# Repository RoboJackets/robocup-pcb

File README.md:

RoboCup PCB Repository
===========
Welcome to the Georgia Tech RoboJackets repository for management and storage of RoboCup's hardware files! Additional information about the team and current projects can be found on the [RoboJackets Website](http://www.robojackets.org/teams/robocup/) and the [RoboJacket Wiki](http://wiki.robojackets.org/w/RoboCup).

If you are a new member to the RoboCup electrical team and have never used *[git version control](http://git-scm.com/)* before, we highly recommend that you familiarize yourself with it by reading [this guide](https://git-scm.com/book/en/v2).

## Prerequisites
- A computer configured with git [[Linux (Preferred)](https://git-scm.com/install/linux)] [[Windows](https://windows.github.com)] [[Mac](https://mac.github.com/)]
- An installation of [KiCAD v10.0](http://kicad-pcb.org/download/)
- An installation of [Obsidian](https://obsidian.md/download)

## Setup

### Cloning the Repository
To clone the repository, run the following command in your terminal:
```
git clone git@github.com:RoboJackets/robocup-pcb.git
```

## Board Archives
All currently deployed boards as of 2026 were designed using KiCAD.

However, older boards in the archives were designed using [EAGLE](http://www.cadsoftusa.com/) or [PCB](http://pcb.geda-project.org) (a program that is part of the [gEDA project](http://www.geda-project.org))

Unfortunately, EAGLE and PCB are no longer supported by their respective companies, and are not available for download. If you need access to these files, you are on your own.

## License

This project is licensed under the Apache License v2.0.  See the [LICENSE](LICENSE) file for more information.

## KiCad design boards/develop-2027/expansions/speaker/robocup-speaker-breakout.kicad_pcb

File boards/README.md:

# Style Guide

## Schematic Style
* Always snap to 0.1 inch grid
* Insert appropriate size frame for each sheet
    * Set Global Attributes for `REVISION` and `TEAM`
    * Set Attribute of frame for `SCH_DESC`

## Board Style
* Attempt to keep snapped to 0.5 mm (with 0.25 alt) with 90º or 45º angles

## Library Style
#### Symbol
* Always keep pins aligned to 0.1 inch grid
* Add Name and Value on correct layers

#### Package
* Add Name and Value on correct layers
* Silkscreen on `TPLACE` should not go over pad
* Use `TDOCU` to show accurate package outline

#### Device
* Final Device ideally be actual part number unless generic part where many possibles could be used
* Use wildcard when using multiple packages with one symbol
* Add correct prefix for component type ([reference](https://en.wikipedia.org/wiki/Reference_designator)), common components:
    * C : Capacitor
    * L : Inductor
    * R : Resistor
    * D : Diodes (including LEDs)
    * J : Jack (least movable part of connector)
    * Q : Transistor
    * F : Fuse
* Add manufacturer part number and (when possible) Digikey part number as attributes `MPN` and `DIGIKEY` respectivly
    * Do this for each technology and variant combination

# Finalize Board

When board completely done and ready to order ensure the following are completed:
* Board folder named "board-name"-v"version"
* Export board to PNG and place in folder
* Create README.md with description of the board and PNG of the board
* Create gerber.zip file of all Gerber files to be sent to board fab
* After all items added for board, make final commit for board version and tag commit as "board-name"-v"version"
* Once pushed to Github create release of board from tag consisting of list of changes from past version, link to gerber.zip (Github raw link for that tag), and PNG of board
    * For prototypes mark release as pre-release

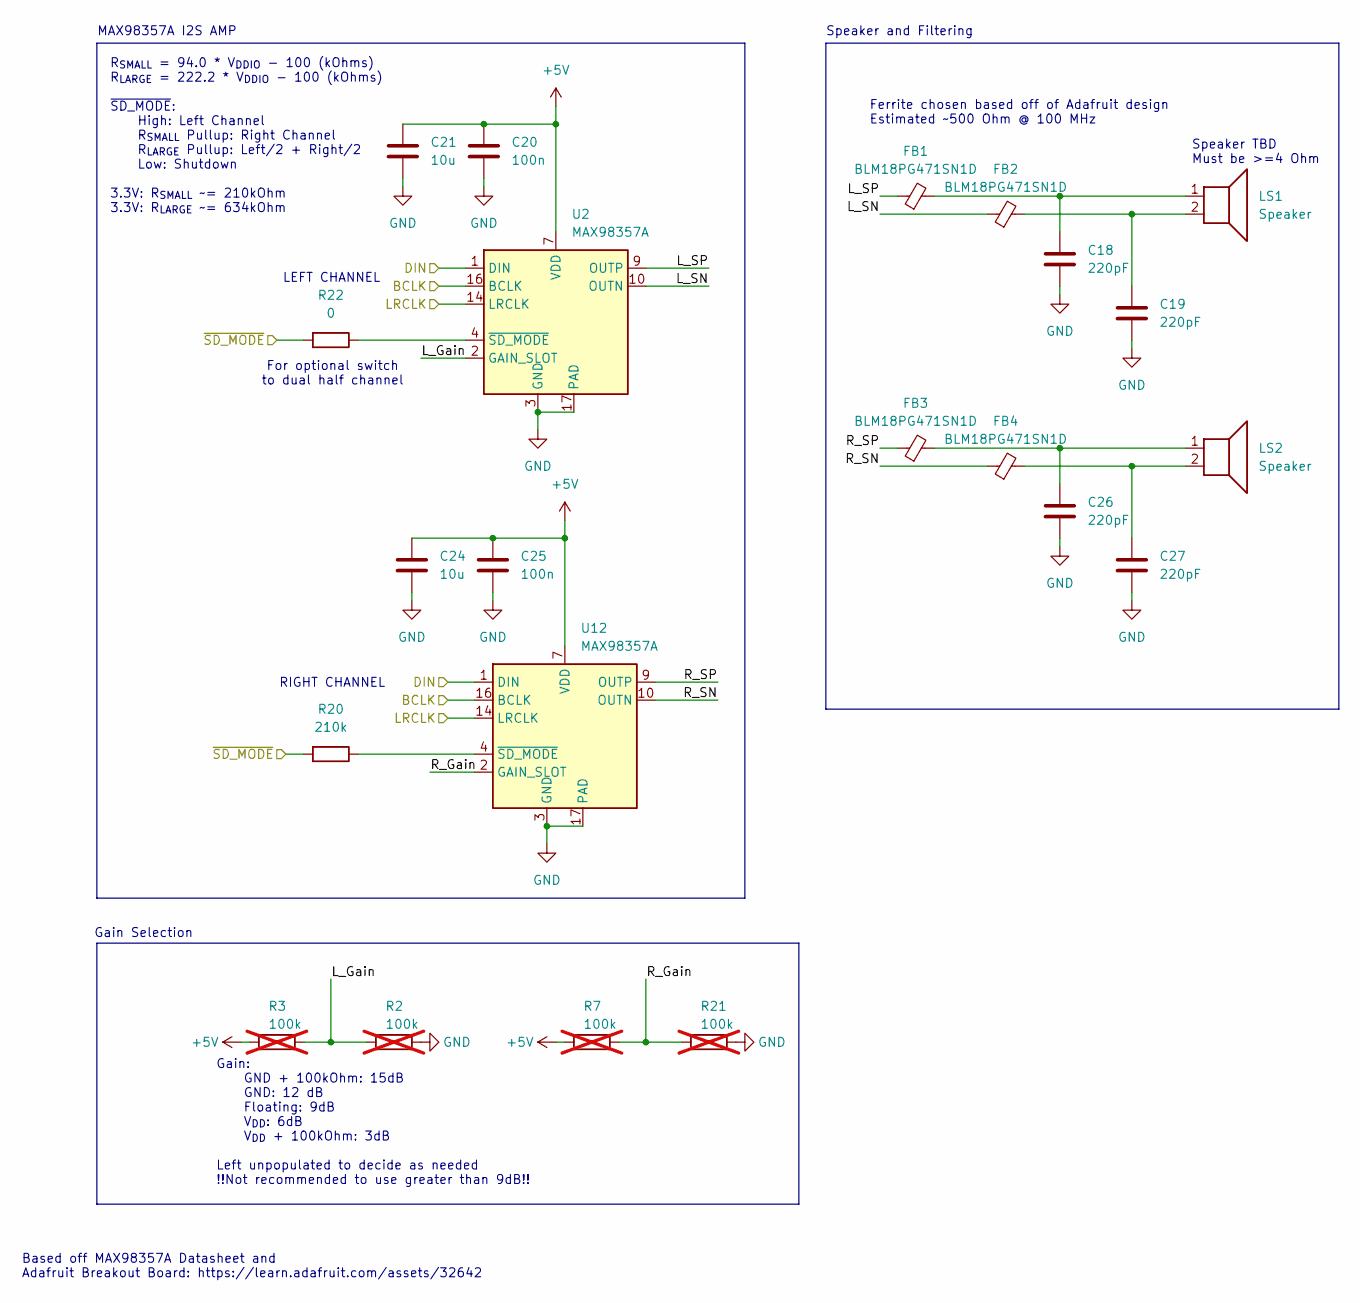
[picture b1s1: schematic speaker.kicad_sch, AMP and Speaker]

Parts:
C18, C19, C26, C27: 220pF; C_0402_1005Metric; Manufacturer P/N GCM1555C1H221FA16D
C20, C25: 100n; C_0402_1005Metric; Manufacturer P/N CC0402JRX7R7BB104
C21, C24: 10u; C_0603_1608Metric; Manufacturer P/N GRM188R61A106ME69J
FB1, FB2, FB3, FB4: BLM18PG471SN1D; L_0603_1608Metric; Manufacturer P/N BLM18PG471SN1D
LS1, LS2: Speaker; JST_GH_SM02B-GHS-TB_1x02-1MP_P1.25mm_Horizontal; Manufacturer P/N SM02B-GHS-TB
R2, R3, R7, R21: 100k; R_0402_1005Metric; Manufacturer P/N ERJ-2GEJ104X; not fitted
R20: 210k; R_0402_1005Metric; Manufacturer P/N RK73H1ETTP2103F
R22: 0; R_0402_1005Metric; Manufacturer P/N ERJ-2GE0R00X
U2, U12: MAX98357A; TQFN-16-1EP_3x3mm_P0.5mm_EP1.23x1.23mm; Manufacturer P/N MAX98357AETE+T

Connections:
+5V: C20.1, C21.1, C24.1, C25.1, R3.1, R7.1, U2.7 (VDD), U2.8 (VDD), U12.7 (VDD), U12.8 (VDD); also elsewhere on the board
/MCU/BCLK: U2.16 (BCLK), U12.16 (BCLK); also elsewhere on the board
/MCU/DIN: U2.1 (DIN), U12.1 (DIN); also elsewhere on the board
/MCU/LRCLK: U2.14 (LRCLK), U12.14 (LRCLK); also elsewhere on the board
/MCU/~SD_MODE: R20.2, R22.2; also elsewhere on the board
/Speaker/L_Gain: R2.1, R3.2, U2.2 (GAIN_SLOT)
/Speaker/L_SN: FB2.1, U2.10 (OUTN)
/Speaker/L_SP: FB1.1, U2.9 (OUTP)
/Speaker/R_Gain: R7.2, R21.1, U12.2 (GAIN_SLOT)
/Speaker/R_SN: FB4.1, U12.10 (OUTN)
/Speaker/R_SP: FB3.1, U12.9 (OUTP)
GND: C18.2, C19.2, C20.2, C21.2, C24.2, C25.2, C26.2, C27.2, R2.2, R21.2, U2.3 (GND), U2.11 (GND), U2.15 (GND), U2.17 (PAD), U12.3 (GND), U12.11 (GND), U12.15 (GND), U12.17 (PAD); also elsewhere on the board
unnamed: C18.1, FB1.2, LS1.1
unnamed: C19.1, FB2.2, LS1.2
unnamed: C26.1, FB3.2, LS2.1
unnamed: C27.1, FB4.2, LS2.2
unnamed: R22.1, U2.4 (~SD_MODE)
unnamed: R20.1, U12.4 (~SD_MODE)

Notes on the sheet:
Based off MAX98357A Datasheet and Adafruit Breakout Board: https://learn.adafruit.com/assets/32642
LEFT CHANNEL
Gain Selection
RIGHT CHANNEL
Ferrite chosen based off of Adafruit design Estimated ~500 Ohm @ 100 MHz
MAX98357A I2S AMP
Speaker TBD Must be >=4 Ohm
R_{SMALL} = 94.0 * V_{DDIO} - 100 (kOhms) R_{LARGE} = 222.2 * V_{DDIO} - 100 (kOhms) ~{SD_MODE}: High: Left Channel R_{SMALL} Pullup: Right Channel R_{LARGE} Pullup: Left/2 + Right/2 Low: Shutdown 3.3V: R_{SMALL} ~= 210kOhm 3.3V: R_{LARGE} ~= 634kOhm
Speaker and Filtering
Gain: GND + 100kOhm: 15dB GND: 12 dB Floating: 9dB V_{DD}: 6dB V_{DD} + 100kOhm: 3dB Left unpopulated to decide as needed !!Not recommended to use greater than 9dB!!
For optional switch to dual half channel

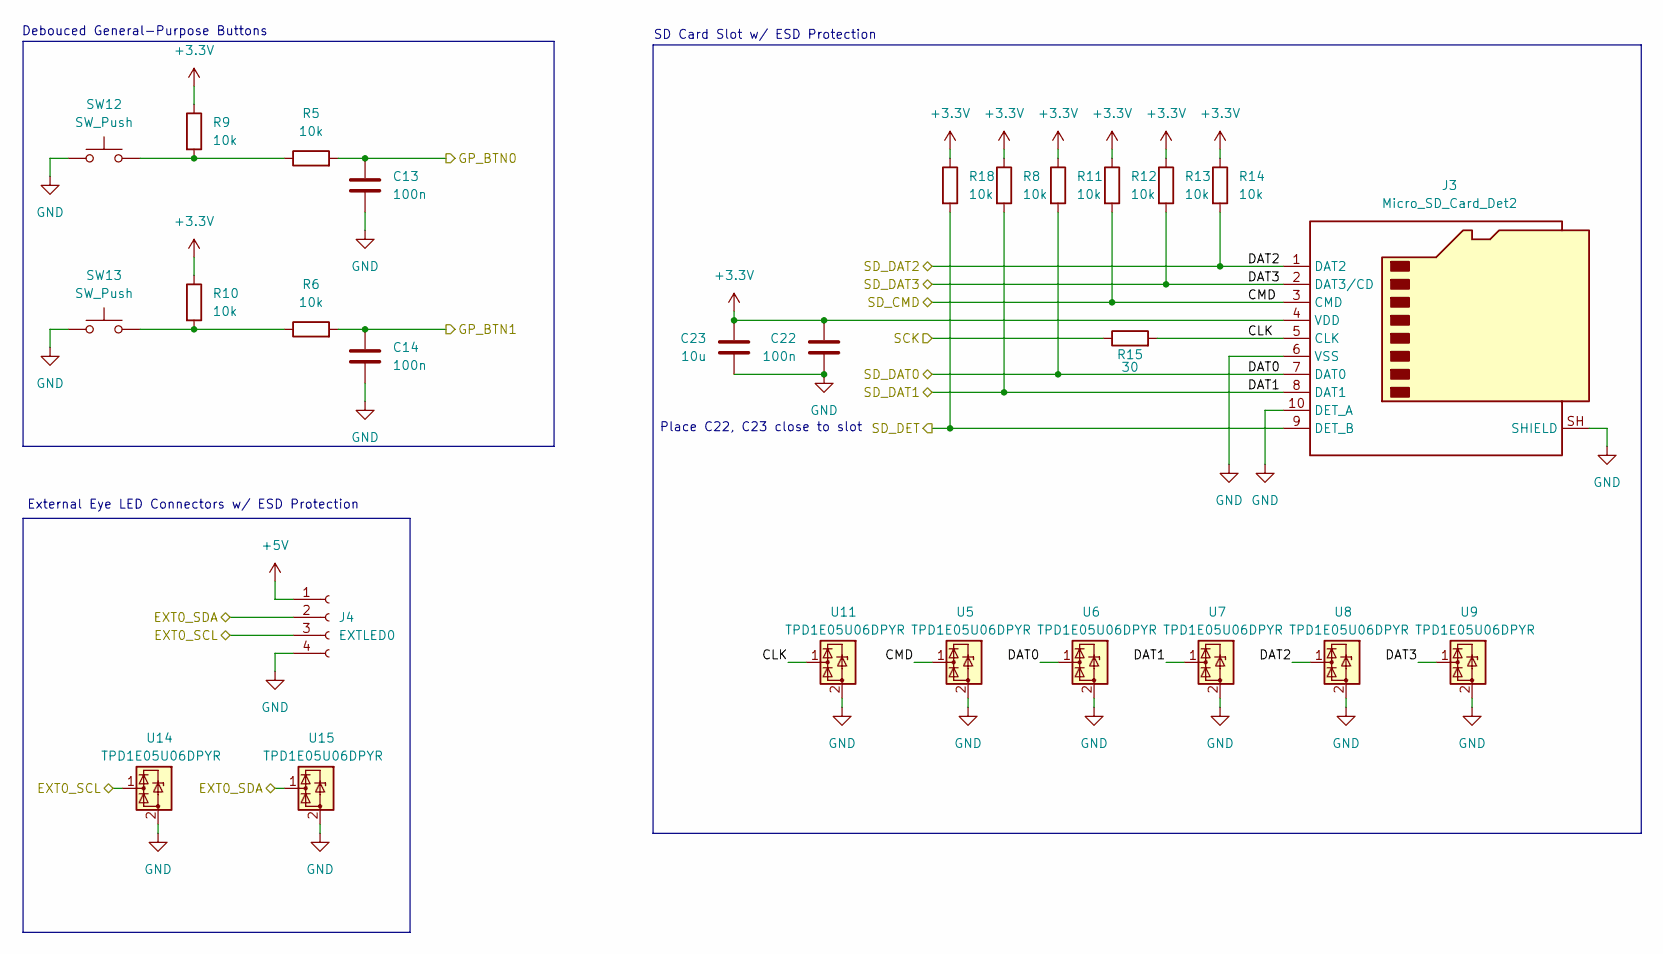
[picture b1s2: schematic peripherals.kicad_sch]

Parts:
C13, C14, C22: 100n; C_0402_1005Metric; Manufacturer P/N CC0402JRX7R7BB104
C23: 10u; C_0603_1608Metric; Manufacturer P/N GRM188R61A106ME69J
J3: Micro_SD_Card_Det2; microSD_HC_Hirose_DM3AT-SF-PEJM5; Manufacturer P/N DM3AT-SF-PEJM5
J4: EXTLED0; JST_GH_SM04B-GHS-TB_1x04-1MP_P1.25mm_Horizontal; Manufacturer P/N SM04B-GHS-TB
R5, R6, R8, R9, R10, R11, R12, R13, R14, R18: 10k; R_0201_0603Metric; Manufacturer P/N RMCF0201FT10K0
R15: 30; R_0201_0603Metric; Manufacturer P/N CR0201-FW-30R0GLF
SW12, SW13: SW_Push; SW_SKRPABE010; Manufacturer P/N SKRPABE010
U5, U6, U7, U8, U9, U11, U14, U15: TPD1E05U06DPYR; Texas_DPY0002A_0.6x1mm_P0.65mm; Manufacturer P/N TPD1E05U06DPYR

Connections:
+3.3V: C22.1, C23.1, J3.4 (VDD), R8.1, R9.1, R10.1, R11.1, R12.1, R13.1, R14.1, R18.1; also elsewhere on the board
+5V: J4.1; also elsewhere on the board
/MCU/GP_BTN0: C13.1, R5.2; also elsewhere on the board
/MCU/GP_BTN1: C14.1, R6.2; also elsewhere on the board
/MCU/I2C1_SCL: J4.3, U14.1 (I/O); also elsewhere on the board
/MCU/I2C1_SDA: J4.2, U15.1 (I/O); also elsewhere on the board
/MCU/SD_CLK: R15.1; also elsewhere on the board
/MCU/SD_DET: J3.9 (DET_B), R18.2; also elsewhere on the board
/Peripherals/CLK: J3.5 (CLK), R15.2, U11.1 (I/O)
/Peripherals/CMD: J3.3 (CMD), R12.2, U5.1 (I/O); also elsewhere on the board
/Peripherals/DAT0: J3.7 (DAT0), R11.2, U6.1 (I/O); also elsewhere on the board
/Peripherals/DAT1: J3.8 (DAT1), R8.2, U7.1 (I/O); also elsewhere on the board
/Peripherals/DAT2: J3.1 (DAT2), R14.2, U8.1 (I/O); also elsewhere on the board
/Peripherals/DAT3: J3.2 (DAT3/CD), R13.2, U9.1 (I/O); also elsewhere on the board
GND: C13.2, C14.2, C22.2, C23.2, J3.6 (VSS), J3.10 (DET_A), J3.SH (SHIELD), J4.4, SW12.1, SW13.1, U5.2 (GND), U6.2 (GND), U7.2 (GND), U8.2 (GND), U9.2 (GND), U11.2 (GND), U14.2 (GND), U15.2 (GND); also elsewhere on the board
unnamed: R5.1, R9.2, SW12.2
unnamed: R6.1, R10.2, SW13.2

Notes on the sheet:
SD Card Slot w/ ESD Protection
Debouced General-Purpose Buttons
External Eye LED Connectors w/ ESD Protection
Place C22, C23 close to slot

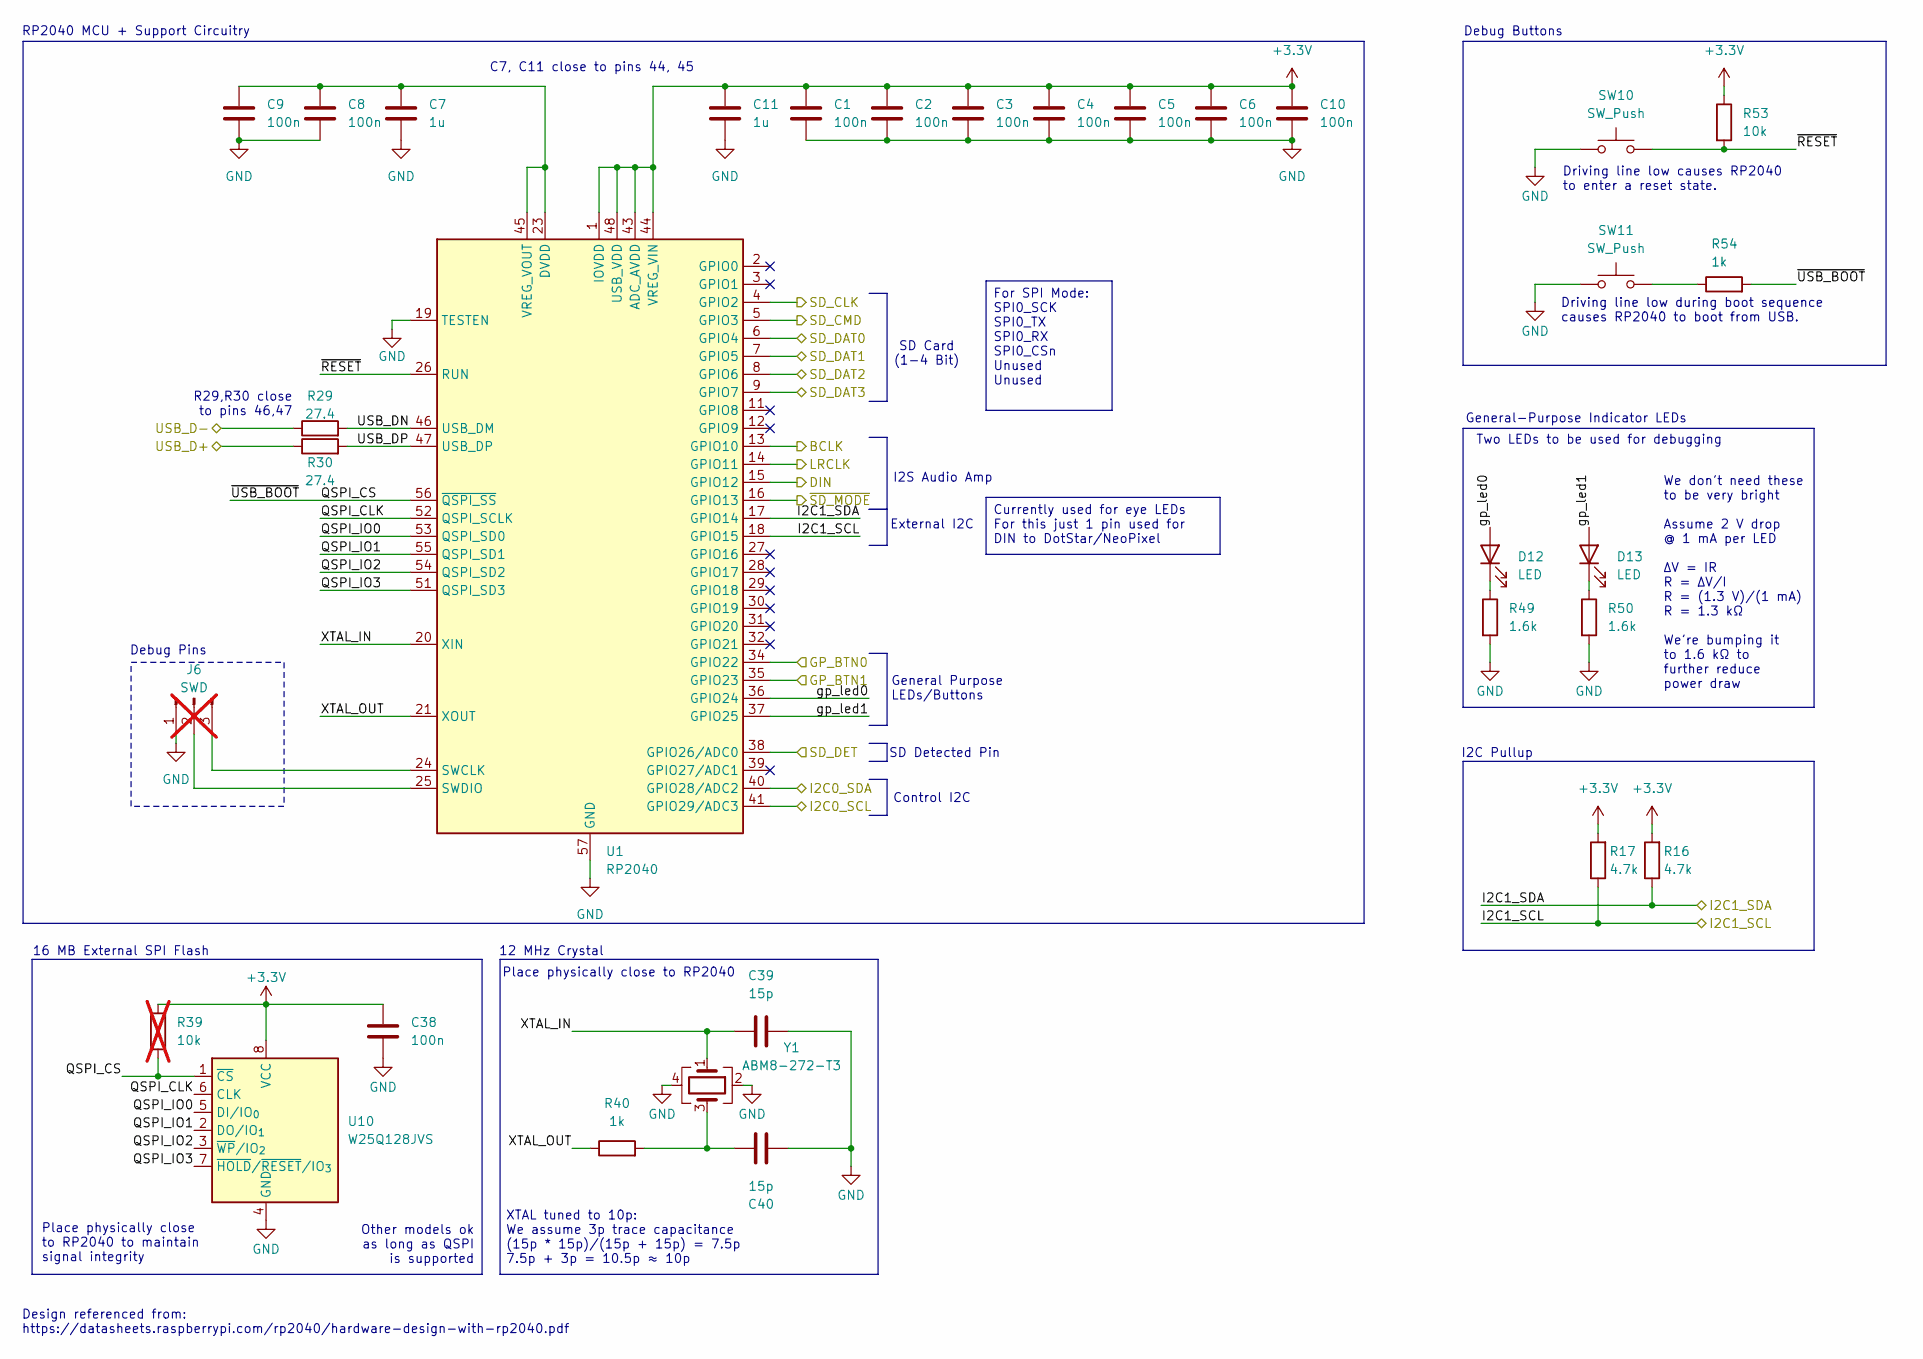
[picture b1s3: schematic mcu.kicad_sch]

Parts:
C1, C2, C3, C4, C5, C6, C8, C9, C10, C38: 100n; C_0402_1005Metric; Manufacturer P/N CC0402JRX7R7BB104
C7, C11: 1u; C_0402_1005Metric; Manufacturer P/N CC0402KRX5R5BB105
C39, C40: 15p; C_0402_1005Metric; Manufacturer P/N GCM1555C1H150FA16J
D12, D13: LED; LED_0603_1608Metric; Manufacturer P/N APT1608EC
J6: SWD; PinHeader_1x03_P1.00mm_Vertical; not fitted
R16, R17: 4.7k; R_0402_1005Metric; Manufacturer P/N RK73H1ETTP4701F
R29, R30: 27.4; R_0201_0603Metric; Manufacturer P/N ERJ-1GNF27R4C
R39: 10k; R_0201_0603Metric; Manufacturer P/N RMCF0201FT10K0; not fitted
R40, R54: 1k; R_0201_0603Metric; Manufacturer P/N RC0201JR-071KL
R49, R50: 1.6k; R_0402_1005Metric; Manufacturer P/N ERJ-2RKF1601X
R53: 10k; R_0201_0603Metric; Manufacturer P/N RMCF0201FT10K0
SW10, SW11: SW_Push; SW_SKRPABE010; Manufacturer P/N SKRPABE010
U1: RP2040; QFN-56-1EP_7x7mm_P0.4mm_EP3.2x3.2mm; Manufacturer P/N SC0914(13)
U10: W25Q128JVS; SOIC-8_5.3x5.3mm_P1.27mm; Manufacturer P/N W25Q128JVS
Y1: ABM8-272-T3; Crystal_SMD_Abracon_ABM8AIG-4Pin_3.2x2.5mm; Manufacturer P/N ABM8-272-T3

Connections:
+3.3V: C1.1, C2.1, C3.1, C4.1, C5.1, C6.1, C10.1, C11.1, C38.1, R16.2, R17.2, R39.1, R53.1, U1.1 (IOVDD), U1.10 (IOVDD), U1.22 (IOVDD), U1.33 (IOVDD), U1.42 (IOVDD), U1.43 (ADC_AVDD), U1.44 (VREG_VIN), U1.48 (USB_VDD), U1.49 (IOVDD), U10.8 (VCC); also elsewhere on the board
/MCU/BCLK: U1.13 (GPIO10); also elsewhere on the board
/MCU/DIN: U1.15 (GPIO12); also elsewhere on the board
/MCU/GP_BTN0: U1.34 (GPIO22); also elsewhere on the board
/MCU/GP_BTN1: U1.35 (GPIO23); also elsewhere on the board
/MCU/I2C0_SCL: U1.41 (GPIO29/ADC3); also elsewhere on the board
/MCU/I2C0_SDA: U1.40 (GPIO28/ADC2); also elsewhere on the board
/MCU/I2C1_SCL: R17.1, U1.18 (GPIO15); also elsewhere on the board
/MCU/I2C1_SDA: R16.1, U1.17 (GPIO14); also elsewhere on the board
/MCU/LRCLK: U1.14 (GPIO11); also elsewhere on the board
/MCU/QSPI_CLK: U1.52 (QSPI_SCLK), U10.6 (CLK)
/MCU/QSPI_CS: R39.2, R54.2, U1.56 (~QSPI_SS), U10.1 (~CS)
/MCU/QSPI_IO0: U1.53 (QSPI_SD0), U10.5 (DI/IO_{0})
/MCU/QSPI_IO1: U1.55 (QSPI_SD1), U10.2 (DO/IO_{1})
/MCU/QSPI_IO2: U1.54 (QSPI_SD2), U10.3 (~WP/IO_{2})
/MCU/QSPI_IO3: U1.51 (QSPI_SD3), U10.7 (~HOLD/~RESET/IO_{3})
/MCU/SD_CLK: U1.4 (GPIO2); also elsewhere on the board
/MCU/SD_DET: U1.38 (GPIO26/ADC0); also elsewhere on the board
/MCU/USB_D+: R30.1; also elsewhere on the board
/MCU/USB_D-: R29.1; also elsewhere on the board
/MCU/USB_DN: R29.2, U1.46 (USB_DM)
/MCU/USB_DP: R30.2, U1.47 (USB_DP)
/MCU/XTAL_IN: C39.2, U1.20 (XIN), Y1.1
/MCU/XTAL_OUT: R40.1, U1.21 (XOUT)
/MCU/gp_led0: D12.2 (A), U1.36 (GPIO24)
/MCU/gp_led1: D13.2 (A), U1.37 (GPIO25)
/MCU/~RESET: R53.2, SW10.2, U1.26 (RUN)
/MCU/~SD_MODE: U1.16 (GPIO13); also elsewhere on the board
/Peripherals/CMD: U1.5 (GPIO3); also elsewhere on the board
/Peripherals/DAT0: U1.6 (GPIO4); also elsewhere on the board
/Peripherals/DAT1: U1.7 (GPIO5); also elsewhere on the board
/Peripherals/DAT2: U1.8 (GPIO6); also elsewhere on the board
/Peripherals/DAT3: U1.9 (GPIO7); also elsewhere on the board
GND: C1.2, C2.2, C3.2, C4.2, C5.2, C6.2, C7.2, C8.2, C9.2, C10.2, C11.2, C38.2, C39.1, C40.2, J6.1, R49.2, R50.2, SW10.1, SW11.1, U1.19 (TESTEN), U1.57 (GND), U10.4 (GND), Y1.2, Y1.4; also elsewhere on the board
unnamed: C40.1, R40.2, Y1.3
unnamed: D12.1 (K), R49.1
unnamed: D13.1 (K), R50.1
unnamed: J6.2, U1.25 (SWDIO)
unnamed: J6.3, U1.24 (SWCLK)
unnamed: R54.1, SW11.2
unnamed: C7.1, C8.1, C9.1, U1.23 (DVDD), U1.45 (VREG_VOUT), U1.50 (DVDD)

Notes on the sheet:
Design referenced from: https://datasheets.raspberrypi.com/rp2040/hardware-design-with-rp2040.pdf
16 MB External SPI Flash
XTAL tuned to 10p: We assume 3p trace capacitance (15p * 15p)/(15p + 15p) = 7.5p 7.5p + 3p = 10.5p ≈ 10p
R29,R30 close to pins 46,47
Place physically close to RP2040 to maintain signal integrity
12 MHz Crystal
I2S Audio Amp
Place physically close to RP2040
Control I2C
General Purpose LEDs/Buttons
Two LEDs to be used for debugging
C7, C11 close to pins 44, 45
General-Purpose Indicator LEDs
External I2C
SD Detected Pin
Debug Pins
Debug Buttons
Driving line low during boot sequence causes RP2040 to boot from USB.
I2C Pullup
We don't need these to be very bright Assume 2 V drop @ 1 mA per LED ΔV = IR R = ΔV/I R = (1.3 V)/(1 mA) R = 1.3 kΩ We're bumping it to 1.6 kΩ to further reduce power draw
Other models ok as long as QSPI is supported
Driving line low causes RP2040 to enter a reset state.
RP2040 MCU + Support Circuitry
SD Card (1-4 Bit)
For SPI Mode: SPI0_SCK SPI0_TX SPI0_RX SPI0_CSn Unused Unused
Currently used for eye LEDs For this just 1 pin used for DIN to DotStar/NeoPixel

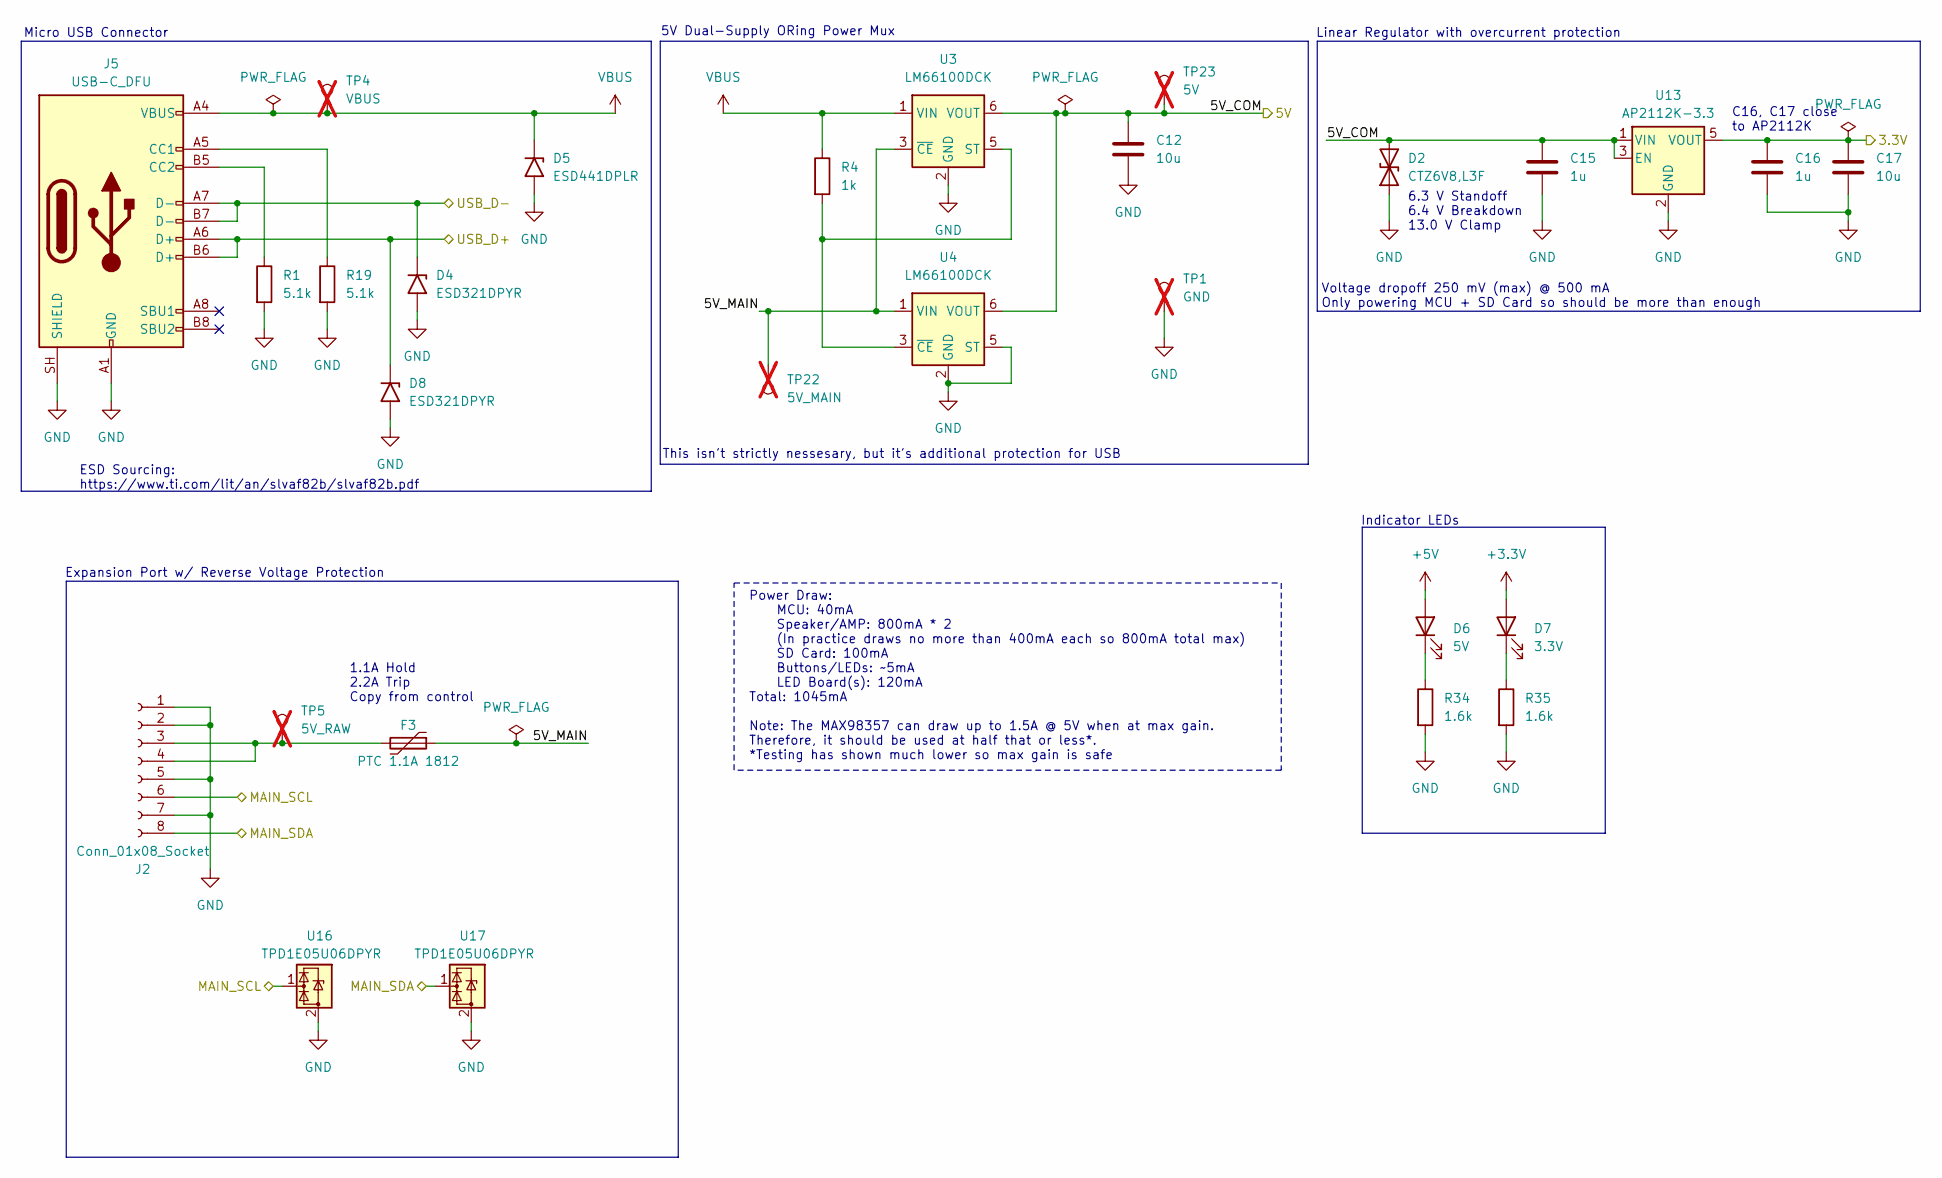
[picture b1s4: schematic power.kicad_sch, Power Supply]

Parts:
C12, C17: 10u; C_0603_1608Metric; Manufacturer P/N GRM188R61A106ME69J
C15, C16: 1u; C_0402_1005Metric; Manufacturer P/N CC0402KRX5R5BB105
D2: CTZ6V8,L3F; D_SOD-882D; Manufacturer P/N CTZ6V8,L3F
D4, D8: ESD321DPYR; D_0402_1005Metric; Manufacturer P/N ESD321DPYR
D5: ESD441DPLR; D_0201_0603Metric; Manufacturer P/N ESD441DPLR
D6: 5V; LED_0603_1608Metric; Manufacturer P/N APT1608EC
D7: 3.3V; LED_0603_1608Metric; Manufacturer P/N APT1608EC
F3: PTC 1.1A 1812; Fuse_Bourns_MF-MSMF_1812; Manufacturer P/N MF-MSMF110/16X-2
J2: Conn_01x08_Socket; JST_GH_SM08B-GHS-TB_1x08-1MP_P1.25mm_Horizontal; Manufacturer P/N SM08B-GHS-TB
J5: USB-C_DFU; USB_C_Receptacle_GCT_USB4110; Manufacturer P/N USB4110-GF-A
R1, R19: 5.1k; R_0201_0603Metric; Manufacturer P/N ERJ-1GNF5101C
R4: 1k; R_0603_1608Metric; Manufacturer P/N RK73H1JTTD1001F
R34, R35: 1.6k; R_0402_1005Metric; Manufacturer P/N ERJ-2RKF1601X
TP1: GND; TestPoint_Pad_D1.0mm; not fitted
TP4: VBUS; TestPoint_Pad_D1.0mm; not fitted
TP5: 5V_RAW; TestPoint_Pad_D1.0mm; not fitted
TP22: 5V_MAIN; TestPoint_Pad_D1.0mm; not fitted
TP23: 5V; TestPoint_Pad_D1.0mm; not fitted
U3, U4: LM66100DCK; SOT-363_SC-70-6; Manufacturer P/N LM66100DCK
U13: AP2112K-3.3; SOT-23-5; Manufacturer P/N AP2112K-3.3TRG1
U16, U17: TPD1E05U06DPYR; Texas_DPY0002A_0.6x1mm_P0.65mm; Manufacturer P/N TPD1E05U06DPYR

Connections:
+3.3V: C16.1, C17.1, D7.2 (A), U13.5 (VOUT); also elsewhere on the board
+5V: C12.1, C15.1, D2.2 (A2), D6.2 (A), TP23.1 (1_1), U3.6 (VOUT), U4.6 (VOUT), U13.1 (VIN), U13.3 (EN); also elsewhere on the board
/MCU/I2C0_SCL: J2.6, U16.1 (I/O); also elsewhere on the board
/MCU/I2C0_SDA: J2.8, U17.1 (I/O); also elsewhere on the board
/MCU/USB_D+: D8.1 (A1), J5.A6 (D+), J5.B6 (D+); also elsewhere on the board
/MCU/USB_D-: D4.1 (A1), J5.A7 (D-), J5.B7 (D-); also elsewhere on the board
/Power/5V_MAIN: F3.1, TP22.1 (1_1), U3.3 (~CE), U4.1 (VIN)
GND: C12.2, C15.2, C16.2, C17.2, D2.1 (A1), D4.2 (A2), D5.2 (A2), D8.2 (A2), J2.1, J2.2, J2.5, J2.7, J5.A1 (GND), J5.A12 (GND), J5.B1 (GND), J5.B12 (GND), J5.SH (SHIELD), R1.2, R19.2, R34.2, R35.2, TP1.1 (1_1), U3.2 (GND), U4.2 (GND), U4.5 (ST), U13.2 (GND), U16.2 (GND), U17.2 (GND); also elsewhere on the board
unnamed: D6.1 (K), R34.1
unnamed: D7.1 (K), R35.1
unnamed: F3.2, J2.3, J2.4, TP5.1 (1_1)
unnamed: J5.A5 (CC1), R19.1
unnamed: J5.B5 (CC2), R1.1
unnamed: R4.2, U3.5 (ST), U4.3 (~CE)
VBUS: D5.1 (A1), J5.A4 (VBUS), J5.A9 (VBUS), J5.B4 (VBUS), J5.B9 (VBUS), R4.1, TP4.1 (1_1), U3.1 (VIN)

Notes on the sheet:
Linear Regulator with overcurrent protection
C16, C17 close to AP2112K
6.3 V Standoff 6.4 V Breakdown 13.0 V Clamp
Micro USB Connector
This isn't strictly nessesary, but it's additional protection for USB
Voltage dropoff 250 mV (max) @ 500 mA Only powering MCU + SD Card so should be more than enough
Indicator LEDs
ESD Sourcing: https://www.ti.com/lit/an/slvaf82b/slvaf82b.pdf
Expansion Port w/ Reverse Voltage Protection
1.1A Hold 2.2A Trip Copy from control
Power Draw: MCU: 40mA Speaker/AMP: 800mA * 2 (In practice draws no more than 400mA each so 800mA total max) SD Card: 100mA Buttons/LEDs: ~5mA LED Board(s): 120mA Total: 1045mA Note: The MAX98357 can draw up to 1.5A @ 5V when at max gain. Therefore, it should be used at half that or less*. *Testing 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
5V Dual-Supply ORing Power Mux

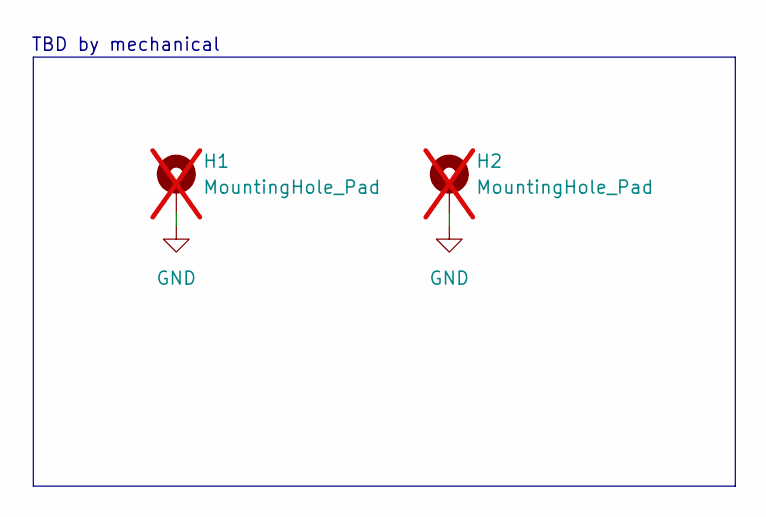
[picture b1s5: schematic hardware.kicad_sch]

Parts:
H1, H2: MountingHole_Pad; MountingHole_2.2mm_M2_DIN965_Pad; not fitted

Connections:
GND: H1.1 (1_1), H2.1 (1_1); also elsewhere on the board

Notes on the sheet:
TBD by mechanical

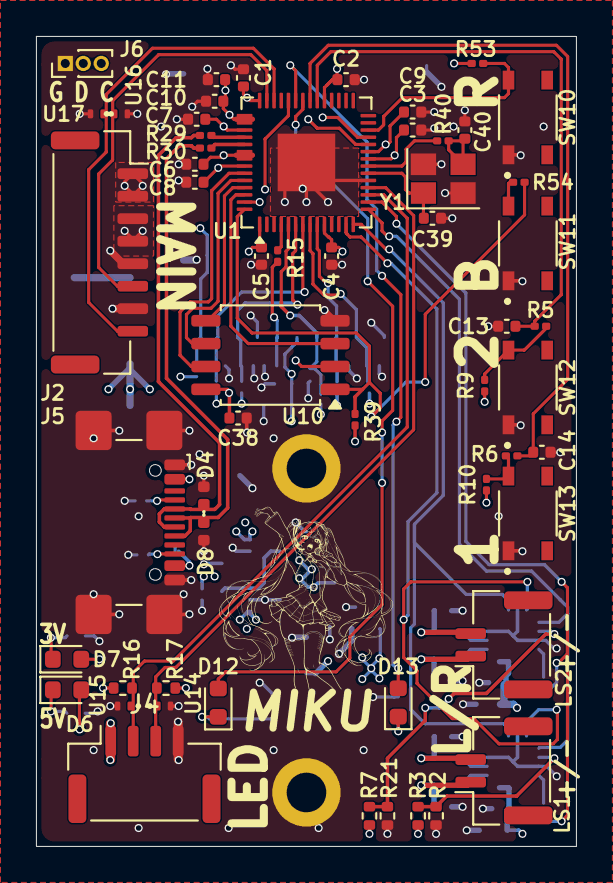
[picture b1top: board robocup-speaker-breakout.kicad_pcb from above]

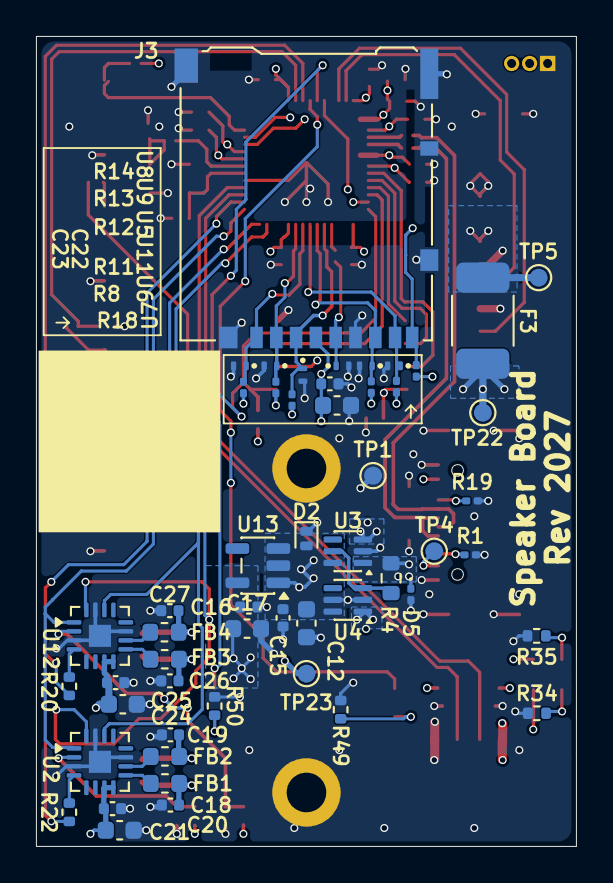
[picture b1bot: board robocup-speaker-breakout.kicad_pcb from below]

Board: 4 copper layers, 30.0 x 45.0 mm, 111 parts (53 on the bottom side), 65 nets.

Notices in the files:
boards/develop-2027/controlboard/compact/ControlBoard2027_C4L2/ControlBoard2027_C4L2.kicad_pcb:
Art: shadok (mod. CC BY 3.0)
